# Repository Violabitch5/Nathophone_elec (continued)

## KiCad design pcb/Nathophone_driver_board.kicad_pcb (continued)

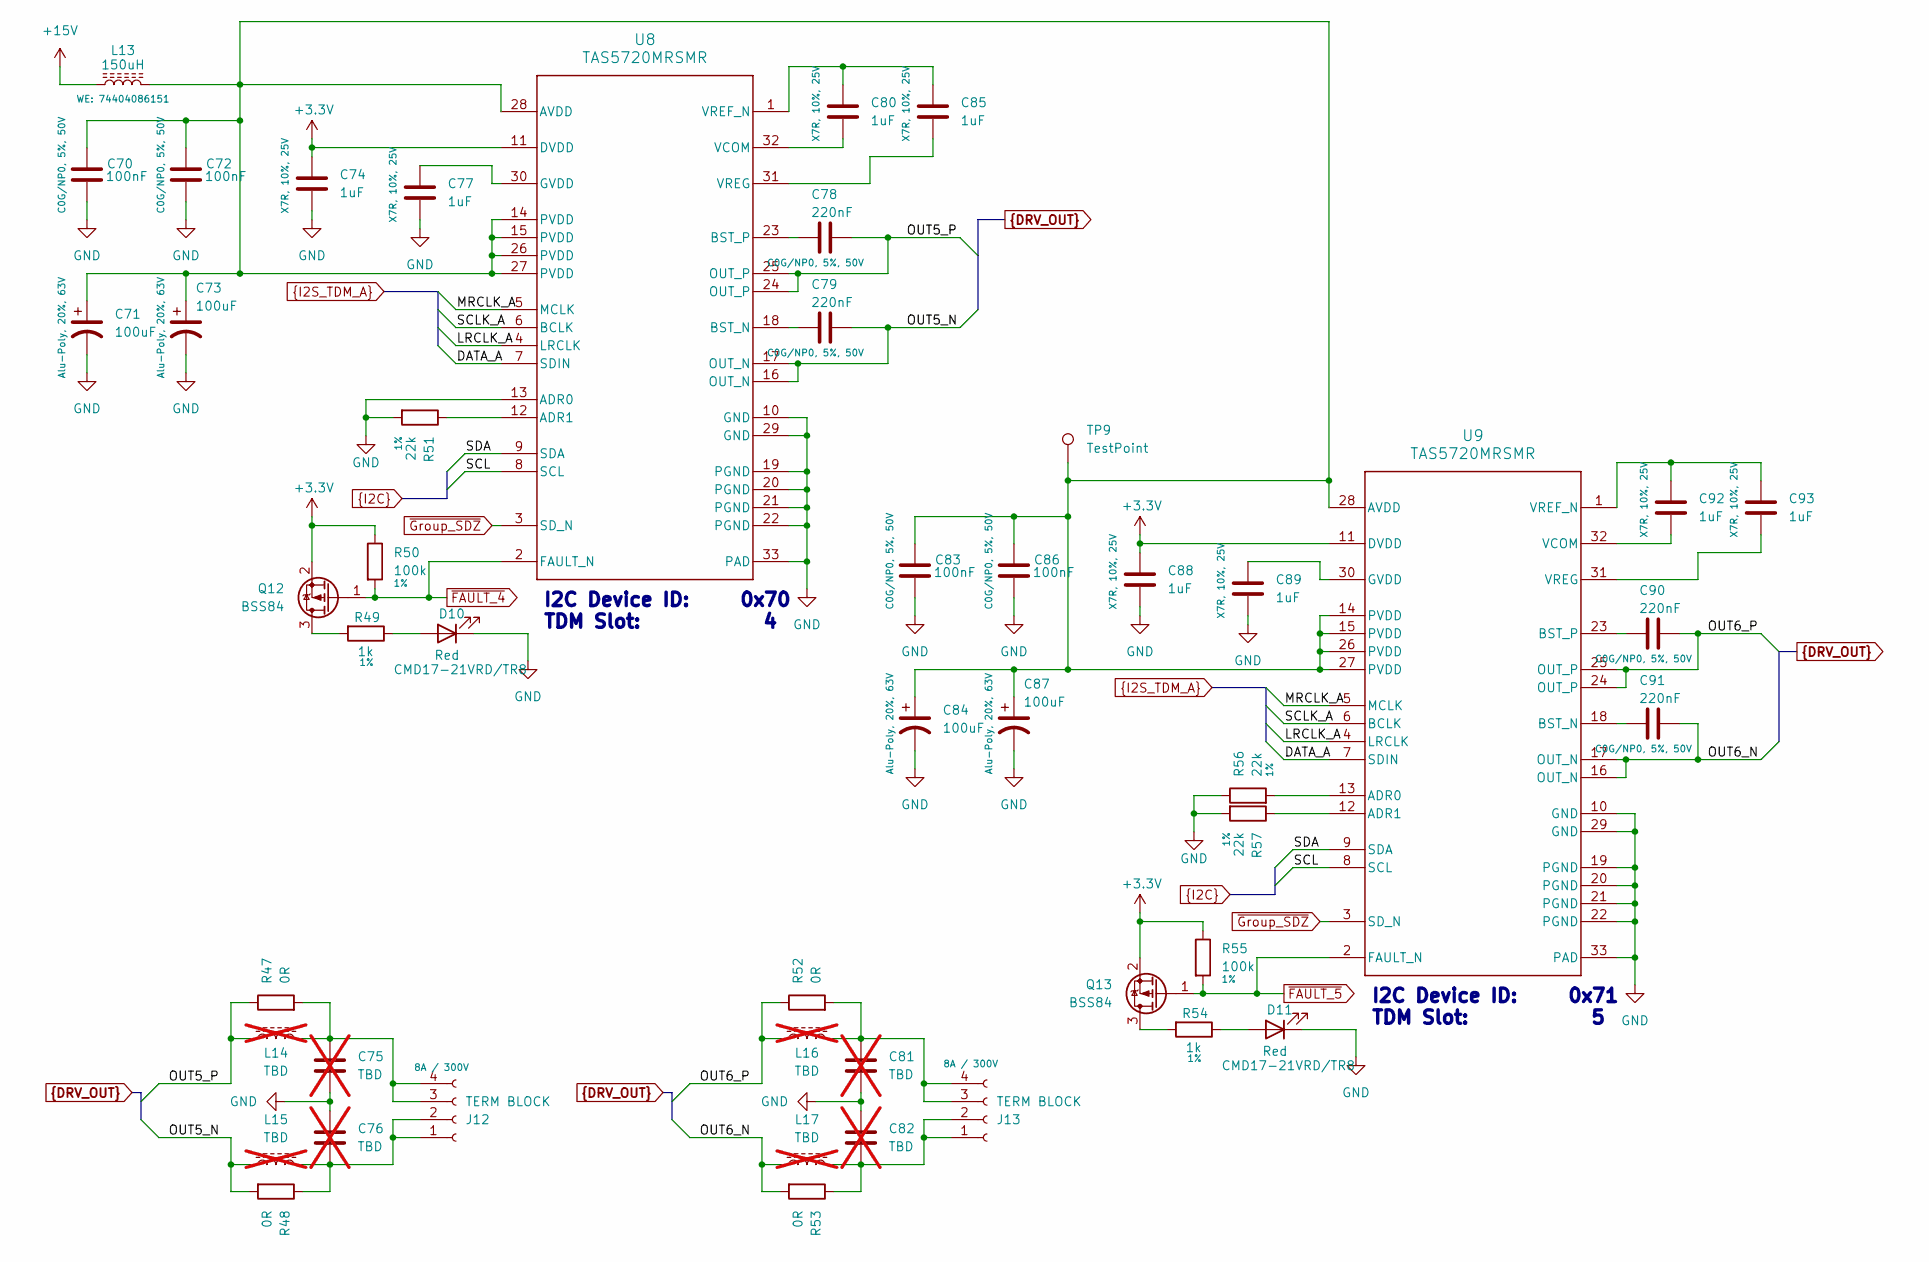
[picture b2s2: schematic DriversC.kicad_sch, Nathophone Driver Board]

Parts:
C70, C72, C83, C86: 100nF; C_1206_3216Metric; MPN GRM3195C1H104JA05D; DigiKey_PartNo 490-GRM3195C1H104JA05DTR-ND
C71, C73, C84, C87: 100uF; C_Elec_10x10.2; MPN A782MS107M1JLAS030; DigiKey_PartNo 399-A782MS107M1JLAS030TR-ND
C74, C77, C80, C85, C88, C89, C92, C93: 1uF; C_0805_2012Metric; MPN CL21B105KAFNNNE; DigiKey_PartNo 1276-1066-2-ND
C75, C76, C81, C82: TBD; C_2220_5750Metric; MPN SMDTC03680QB00MP00; DigiKey_PartNo 1928-1932-2-ND; not fitted
C78, C79, C90, C91: 220nF; C_1206_3216Metric; MPN GRM31C5C1H224JE02L; DigiKey_PartNo 490-GRM31C5C1H224JE02LTR-ND
D10, D11: CMD17-21VRD/TR8; LED_0805_2012Metric; MPN CMD17-21VRD/TR8; DigiKey_PartNo L62501TR-ND
J12, J13: TERM BLOCK; CONN_1862042; MPN 1862042; DigiKey_PartNo 277-12154-ND
L13: 150uH; WE-LQS_8065; MPN 74404086151; DigiKey_PartNo 732-11733-2-ND
L14, L15, L16, L17: TBD; IND_SRU1048-150Y; MPN SRU1048-150Y; DigiKey_PartNo SRU1048-150YTR-ND; not fitted
Q12, Q13: BSS84; SOT-23; MPN BSS84; DigiKey_PartNo 5399-BSS84TR-ND
R47, R48, R52, R53: 0R; R_2010_5025Metric; MPN CRCW20100000Z0EF; DigiKey_PartNo 541-0.0WTR-ND
R49, R54: 1k; R_0805_2012Metric; MPN CRCW08051K00FKEA; DigiKey_PartNo 541-1.00KCTR-ND
R50, R55: 100k; R_0805_2012Metric; MPN CRCW0805100KFKEA; DigiKey_PartNo 541-100KCTR-ND
R51, R56, R57: 22k; R_0805_2012Metric; MPN CRCW080522K0FKEB; DigiKey_PartNo 541-CRCW080522K0FKEBTR-ND
TP9: TestPoint; TestPoint_Pad_D2.0mm
U8, U9: TAS5720MRSMR; VQFN32_RSM0032B_NV; MPN TAS5720MRSMR; DigiKey_PartNo 296-TAS5720MRSMRTR-ND

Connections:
+3.3V: C74.1, C88.1, Q12.2 (S), Q13.2 (S), R50.1, R55.1, U8.11 (DVDD), U9.11 (DVDD); also elsewhere on the board
+15V: L13.1; also elsewhere on the board
DATA_A: U8.7 (SDIN), U9.7 (SDIN); also elsewhere on the board
GND: C70.2, C71.2, C72.2, C73.2, C74.2, C75.2, C76.1, C77.2, C81.2, C82.1, C83.2, C84.2, C86.2, C87.2, C88.2, C89.2, D10.1 (K), D11.1 (K), R51.2, R56.1, R57.2, U8.10 (GND), U8.13 (ADR0), U8.19 (PGND), U8.20 (PGND), U8.21 (PGND), U8.22 (PGND), U8.29 (GND), U8.33 (PAD), U9.10 (GND), U9.19 (PGND), U9.20 (PGND), U9.21 (PGND), U9.22 (PGND), U9.29 (GND), U9.33 (PAD); also elsewhere on the board
LRCLK_A: U8.4 (LRCLK), U9.4 (LRCLK); also elsewhere on the board
MRCLK_A: U8.5 (MCLK), U9.5 (MCLK); also elsewhere on the board
unnamed: D10.2 (A), R49.1
unnamed: D11.2 (A), R54.1
unnamed: C76.2, J12.1, J12.2, L15.2, R48.1
unnamed: C75.1, J12.3, J12.4, L14.2, R47.2
unnamed: C82.2, J13.1, J13.2, L17.2, R53.1
unnamed: C81.1, J13.3, J13.4, L16.2, R52.2
unnamed: Q12.3 (D), R49.2
unnamed: Q13.3 (D), R54.2
unnamed: R51.1, U8.12 (ADR1)
unnamed: C70.1, C71.1, C72.1, C73.1, C83.1, C84.1, C86.1, C87.1, L13.2, TP9.1, U8.14 (PVDD), U8.15 (PVDD), U8.26 (PVDD), U8.27 (PVDD), U8.28 (AVDD), U9.14 (PVDD), U9.15 (PVDD), U9.26 (PVDD), U9.27 (PVDD), U9.28 (AVDD)
unnamed: C79.1, U8.18 (BST_N)
unnamed: C78.1, U8.23 (BST_P)
unnamed: C77.1, U8.30 (GVDD)
unnamed: C80.2, U8.32 (VCOM)
unnamed: C80.1, C85.1, U8.1 (VREF_N)
unnamed: C85.2, U8.31 (VREG)
unnamed: R56.2, U9.13 (ADR0)
unnamed: R57.1, U9.12 (ADR1)
unnamed: C91.1, U9.18 (BST_N)
unnamed: C90.1, U9.23 (BST_P)
unnamed: C89.1, U9.30 (GVDD)
unnamed: C92.2, U9.32 (VCOM)
unnamed: C92.1, C93.1, U9.1 (VREF_N)
unnamed: C93.2, U9.31 (VREG)
OUT5_N: C79.2, L15.1, R48.2, U8.16 (OUT_N), U8.17 (OUT_N); also elsewhere on the board
OUT5_P: C78.2, L14.1, R47.1, U8.24 (OUT_P), U8.25 (OUT_P); also elsewhere on the board
OUT6_N: C91.2, L17.1, R53.2, U9.16 (OUT_N), U9.17 (OUT_N); also elsewhere on the board
OUT6_P: C90.2, L16.1, R52.1, U9.24 (OUT_P), U9.25 (OUT_P); also elsewhere on the board
SCL: U8.8 (SCL), U9.8 (SCL); also elsewhere on the board
SCLK_A: U8.6 (BCLK), U9.6 (BCLK); also elsewhere on the board
SDA: U8.9 (SDA), U9.9 (SDA); also elsewhere on the board
~FAULT_4: Q12.1 (G), R50.2, U8.2 (FAULT_N); also elsewhere on the board
~FAULT_5: Q13.1 (G), R55.2, U9.2 (FAULT_N); also elsewhere on the board
~Group_SDZ: U8.3 (SD_N), U9.3 (SD_N); also elsewhere on the board

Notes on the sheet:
I2C Device ID: 0x70 TDM Slot: 4
I2C Device ID: 0x71 TDM Slot: 5

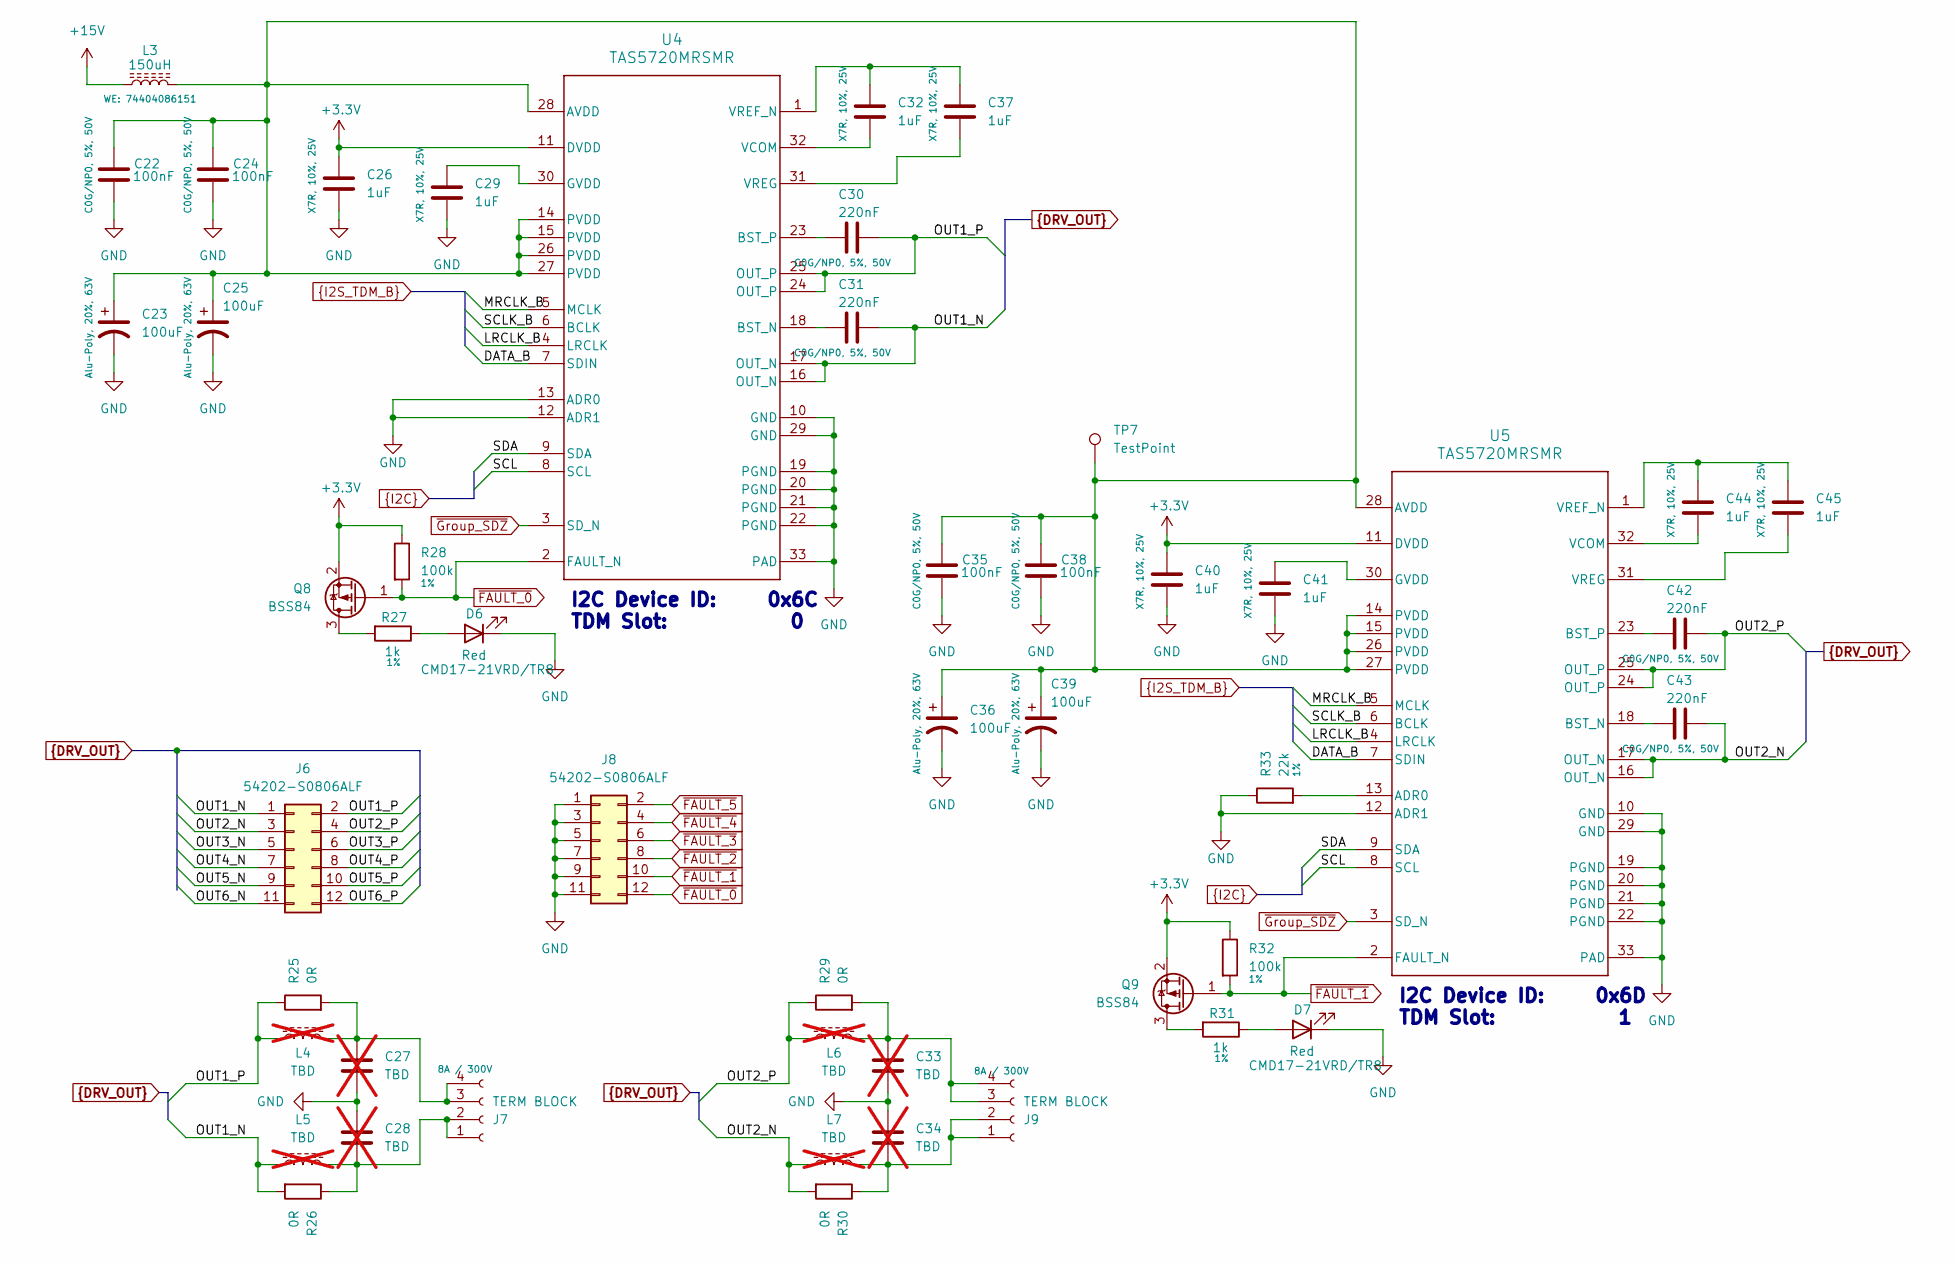
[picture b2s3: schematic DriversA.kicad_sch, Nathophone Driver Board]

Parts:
C22, C24, C35, C38: 100nF; C_1206_3216Metric; MPN GRM3195C1H104JA05D; DigiKey_PartNo 490-GRM3195C1H104JA05DTR-ND
C23, C25, C36, C39: 100uF; C_Elec_10x10.2; MPN A782MS107M1JLAS030; DigiKey_PartNo 399-A782MS107M1JLAS030TR-ND
C26, C29, C32, C37, C40, C41, C44, C45: 1uF; C_0805_2012Metric; MPN CL21B105KAFNNNE; DigiKey_PartNo 1276-1066-2-ND
C27, C28, C33, C34: TBD; C_2220_5750Metric; MPN SMDTC03680QB00MP00; DigiKey_PartNo 1928-1932-2-ND; not fitted
C30, C31, C42, C43: 220nF; C_1206_3216Metric; MPN GRM31C5C1H224JE02L; DigiKey_PartNo 490-GRM31C5C1H224JE02LTR-ND
D6, D7: CMD17-21VRD/TR8; LED_0805_2012Metric; MPN CMD17-21VRD/TR8; DigiKey_PartNo L62501TR-ND
J6, J8: 54202-S0806ALF; PinHeader_2x06_P2.54mm_Vertical_SMD; MPN 54202-S0806ALF; DigiKey_PartNo 609-54202-S0806ALFTR-ND
J7, J9: TERM BLOCK; CONN_1862042; MPN 1862042; DigiKey_PartNo 277-12154-ND
L3: 150uH; WE-LQS_8065; MPN 74404086151; DigiKey_PartNo 732-11733-2-ND
L4, L5, L6, L7: TBD; IND_SRU1048-150Y; MPN SRU1048-150Y; DigiKey_PartNo SRU1048-150YTR-ND; not fitted
Q8, Q9: BSS84; SOT-23; MPN BSS84; DigiKey_PartNo 5399-BSS84TR-ND
R25, R26, R29, R30: 0R; R_2010_5025Metric; MPN CRCW20100000Z0EF; DigiKey_PartNo 541-0.0WTR-ND
R27, R31: 1k; R_0805_2012Metric; MPN CRCW08051K00FKEA; DigiKey_PartNo 541-1.00KCTR-ND
R28, R32: 100k; R_0805_2012Metric; MPN CRCW0805100KFKEA; DigiKey_PartNo 541-100KCTR-ND
R33: 22k; R_0805_2012Metric; MPN CRCW080522K0FKEB; DigiKey_PartNo 541-CRCW080522K0FKEBTR-ND
TP7: TestPoint; TestPoint_Pad_D2.0mm
U4, U5: TAS5720MRSMR; VQFN32_RSM0032B_NV; MPN TAS5720MRSMR; DigiKey_PartNo 296-TAS5720MRSMRTR-ND

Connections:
+3.3V: C26.1, C40.1, Q8.2 (S), Q9.2 (S), R28.1, R32.1, U4.11 (DVDD), U5.11 (DVDD); also elsewhere on the board
+15V: L3.1; also elsewhere on the board
DATA_B: U4.7 (SDIN), U5.7 (SDIN); also elsewhere on the board
GND: C22.2, C23.2, C24.2, C25.2, C26.2, C27.2, C28.1, C29.2, C33.2, C34.1, C35.2, C36.2, C38.2, C39.2, C40.2, C41.2, D6.1 (K), D7.1 (K), J8.1, J8.3, J8.5, J8.7, J8.9, J8.11, R33.1, U4.10 (GND), U4.12 (ADR1), U4.13 (ADR0), U4.19 (PGND), U4.20 (PGND), U4.21 (PGND), U4.22 (PGND), U4.29 (GND), U4.33 (PAD), U5.10 (GND), U5.12 (ADR1), U5.19 (PGND), U5.20 (PGND), U5.21 (PGND), U5.22 (PGND), U5.29 (GND), U5.33 (PAD); also elsewhere on the board
LRCLK_B: U4.4 (LRCLK), U5.4 (LRCLK); also elsewhere on the board
MRCLK_B: U4.5 (MCLK), U5.5 (MCLK); also elsewhere on the board
unnamed: D6.2 (A), R27.1
unnamed: D7.2 (A), R31.1
unnamed: C28.2, J7.1, J7.2, L5.2, R26.1
unnamed: C27.1, J7.3, J7.4, L4.2, R25.2
unnamed: C34.2, J9.1, J9.2, L7.2, R30.1
unnamed: C33.1, J9.3, J9.4, L6.2, R29.2
unnamed: Q8.3 (D), R27.2
unnamed: Q9.3 (D), R31.2
unnamed: C22.1, C23.1, C24.1, C25.1, C35.1, C36.1, C38.1, C39.1, L3.2, TP7.1, U4.14 (PVDD), U4.15 (PVDD), U4.26 (PVDD), U4.27 (PVDD), U4.28 (AVDD), U5.14 (PVDD), U5.15 (PVDD), U5.26 (PVDD), U5.27 (PVDD), U5.28 (AVDD)
unnamed: C31.1, U4.18 (BST_N)
unnamed: C30.1, U4.23 (BST_P)
unnamed: C29.1, U4.30 (GVDD)
unnamed: C32.2, U4.32 (VCOM)
unnamed: C32.1, C37.1, U4.1 (VREF_N)
unnamed: C37.2, U4.31 (VREG)
unnamed: R33.2, U5.13 (ADR0)
unnamed: C43.1, U5.18 (BST_N)
unnamed: C42.1, U5.23 (BST_P)
unnamed: C41.1, U5.30 (GVDD)
unnamed: C44.2, U5.32 (VCOM)
unnamed: C44.1, C45.1, U5.1 (VREF_N)
unnamed: C45.2, U5.31 (VREG)
OUT1_N: C31.2, J6.1, L5.1, R26.2, U4.16 (OUT_N), U4.17 (OUT_N)
OUT1_P: C30.2, J6.2, L4.1, R25.1, U4.24 (OUT_P), U4.25 (OUT_P)
OUT2_N: C43.2, J6.3, L7.1, R30.2, U5.16 (OUT_N), U5.17 (OUT_N)
OUT2_P: C42.2, J6.4, L6.1, R29.1, U5.24 (OUT_P), U5.25 (OUT_P)
OUT3_N: J6.5; also elsewhere on the board
OUT3_P: J6.6; also elsewhere on the board
OUT4_N: J6.7; also elsewhere on the board
OUT4_P: J6.8; also elsewhere on the board
OUT5_N: J6.9; also elsewhere on the board
OUT5_P: J6.10; also elsewhere on the board
OUT6_N: J6.11; also elsewhere on the board
OUT6_P: J6.12; also elsewhere on the board
SCL: U4.8 (SCL), U5.8 (SCL); also elsewhere on the board
SCLK_B: U4.6 (BCLK), U5.6 (BCLK); also elsewhere on the board
SDA: U4.9 (SDA), U5.9 (SDA); also elsewhere on the board
~FAULT_0: J8.12, Q8.1 (G), R28.2, U4.2 (FAULT_N)
~FAULT_1: J8.10, Q9.1 (G), R32.2, U5.2 (FAULT_N)
~FAULT_2: J8.8; also elsewhere on the board
~FAULT_3: J8.6; also elsewhere on the board
~FAULT_4: J8.4; also elsewhere on the board
~FAULT_5: J8.2; also elsewhere on the board
~Group_SDZ: U4.3 (SD_N), U5.3 (SD_N); also elsewhere on the board

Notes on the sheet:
I2C Device ID: 0x6C TDM Slot: 0
I2C Device ID: 0x6D TDM Slot: 1

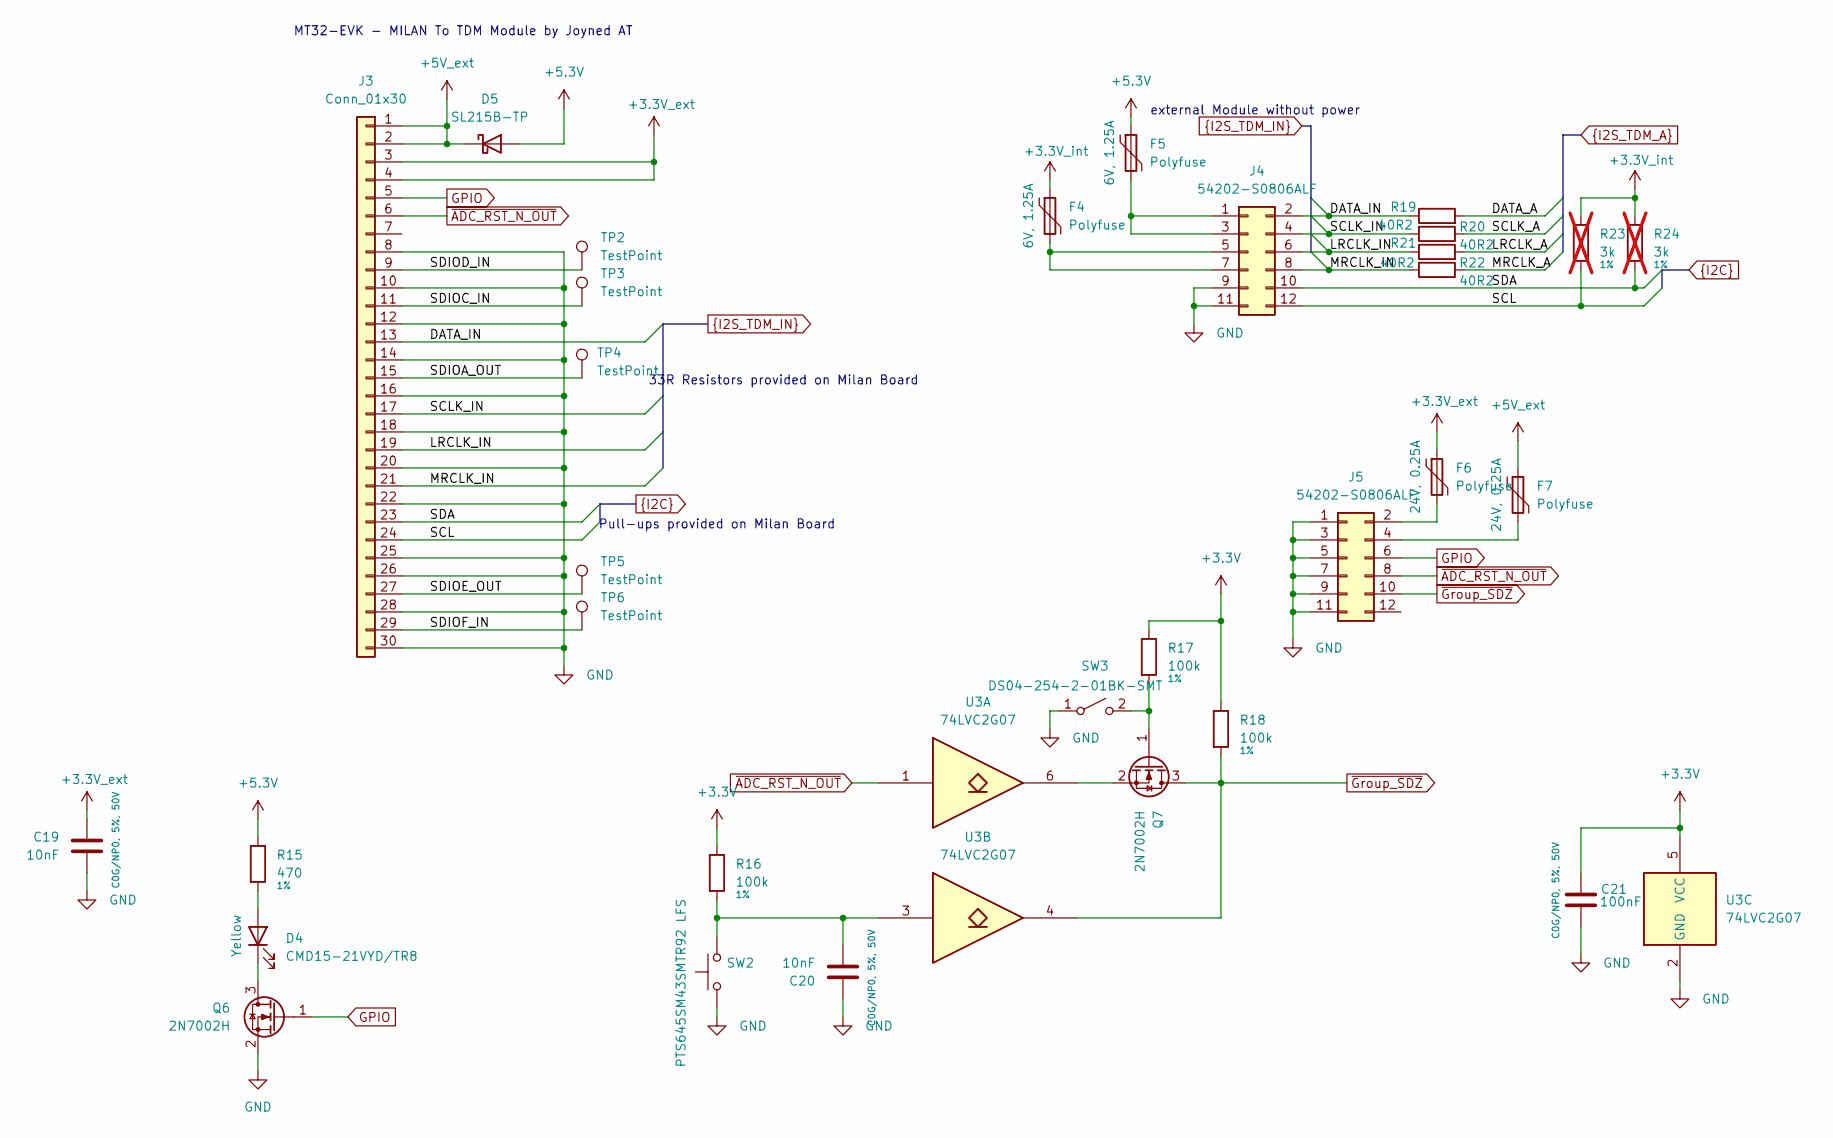
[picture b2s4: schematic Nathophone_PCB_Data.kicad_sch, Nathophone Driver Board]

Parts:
C19, C20: 10nF; C_0805_2012Metric; MPN CL21C103JBF1PNE; DigiKey_PartNo 1276-6790-2-ND
C21: 100nF; C_1206_3216Metric; MPN GRM3195C1H104JA05D; DigiKey_PartNo 490-GRM3195C1H104JA05DTR-ND
D4: CMD15-21VYD/TR8; LED_1206_3216Metric; MPN CMD15-21VYD/TR8; DigiKey_PartNo L62307TR-ND
D5: SL215B-TP; D_SMB; MPN SL215B-TP; DigiKey_PartNo 353-SL215B-TPTR-ND
F4, F5: Polyfuse; Fuse_1812_4532Metric; MPN MINISMDC125F-2; DigiKey_PartNo MINISMDC125F-2TR-ND
F6, F7: Polyfuse; Fuse_1206_3216Metric; MPN 0ZCJ0025AF2E; DigiKey_PartNo 5923-0ZCJ0025AF2ETR-ND
J3: Conn_01x30; CON_525593072_MOL; MPN 0525593072; DigiKey_PartNo 900-0525593072TR-ND
J4, J5: 54202-S0806ALF; PinHeader_2x06_P2.54mm_Vertical_SMD; MPN 54202-S0806ALF; DigiKey_PartNo 609-54202-S0806ALFTR-ND
Q6, Q7: 2N7002H; SOT-23; MPN 2N7002H-7; DigiKey_PartNo 2N7002H-7DITR-ND
R15: 470; R_0805_2012Metric; MPN CRCW0805470RJNEA; DigiKey_PartNo 541-470ATR-ND
R16, R17, R18: 100k; R_0805_2012Metric; MPN CRCW0805100KFKEA; DigiKey_PartNo 541-100KCTR-ND
R19, R20, R21, R22: 40R2; R_0805_2012Metric; MPN CRCW080540R2FKEA; DigiKey_PartNo 541-40.2CTR-ND
R23, R24: 3k; R_0805_2012Metric; MPN CRCW08053K00FKEA; DigiKey_PartNo 541-3.00KCTR-ND; not fitted
SW2: PTS645SM43SMTR92 LFS; SW_SPST_PTS645Sx43SMTR92; MPN PTS645SM43SMTR92 LFS; DigiKey_PartNo CKN9112TR-ND
SW3: DS04-254-2-01BK-SMT; SW_DS04-254-2-01BK-SMT; MPN DS04-254-2-01BK-SMT; DigiKey_PartNo 2223-DS04-254-2-01BK-SMT-ND
TP2, TP3, TP4, TP5, TP6: TestPoint; TestPoint_Pad_D2.0mm
U3: 74LVC2G07; SOT65P210X110-6N; MPN SN74LVC2G07DCKR; DigiKey_PartNo 296-13495-2-ND

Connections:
+3.3V: C21.1, R16.1, R17.1, R18.1, U3.5 (VCC); also elsewhere on the board
+3.3V_ext: C19.1, F6.1, J3.3, J3.4; also elsewhere on the board
+3.3V_int: F4.1, R23.1, R24.1; also elsewhere on the board
+5.3V: D5.2 (A), F5.1, R15.1; also elsewhere on the board
+5V_ext: D5.1 (K), F7.1, J3.1, J3.2
/Data+Power Connections/SDIOA_OUT: J3.15, TP4.1
/Data+Power Connections/SDIOC_IN: J3.11, TP3.1
/Data+Power Connections/SDIOD_IN: J3.9, TP2.1
/Data+Power Connections/SDIOE_OUT: J3.27, TP5.1
/Data+Power Connections/SDIOF_IN: J3.29, TP6.1
DATA_A: R19.2; also elsewhere on the board
DATA_IN: J3.13, J4.2, R19.1
GND: C19.2, C20.1, C21.2, J3.8, J3.10, J3.12, J3.14, J3.16, J3.18, J3.20, J3.22, J3.25, J3.26, J3.28, J3.30, J4.9, J4.11, J5.1, J5.3, J5.5, J5.7, J5.9, J5.11, Q6.2 (S), SW2.1, SW3.1 (A), U3.2 (GND); also elsewhere on the board
GPIO: J3.5, J5.6, Q6.1 (G)
LRCLK_A: R21.2; also elsewhere on the board
LRCLK_IN: J3.19, J4.6, R21.1
MRCLK_A: R22.1; also elsewhere on the board
MRCLK_IN: J3.21, J4.8, R22.2
unnamed: C20.2, R16.2, SW2.2, U3.3
unnamed: D4.2 (A), R15.2
unnamed: D4.1 (K), Q6.3 (D)
unnamed: F5.2, J4.1, J4.3
unnamed: F4.2, J4.5, J4.7
unnamed: F6.2, J5.2
unnamed: F7.2, J5.4
unnamed: Q7.1 (G), R17.2, SW3.2 (B)
unnamed: Q7.2 (S), U3.6
SCL: J3.24, J4.12, R23.2; also elsewhere on the board
SCLK_A: R20.1; also elsewhere on the board
SCLK_IN: J3.17, J4.4, R20.2
SDA: J3.23, J4.10, R24.2; also elsewhere on the board
~ADC_RST_N_OUT: J3.6, J5.8, U3.1
~Group_SDZ: J5.10, Q7.3 (D), R18.2, U3.4; also elsewhere on the board

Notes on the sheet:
MT32-EVK - MILAN To TDM Module by Joyned AT
external Module without power
33R Resistors provided on Milan Board
Pull-ups provided on Milan Board

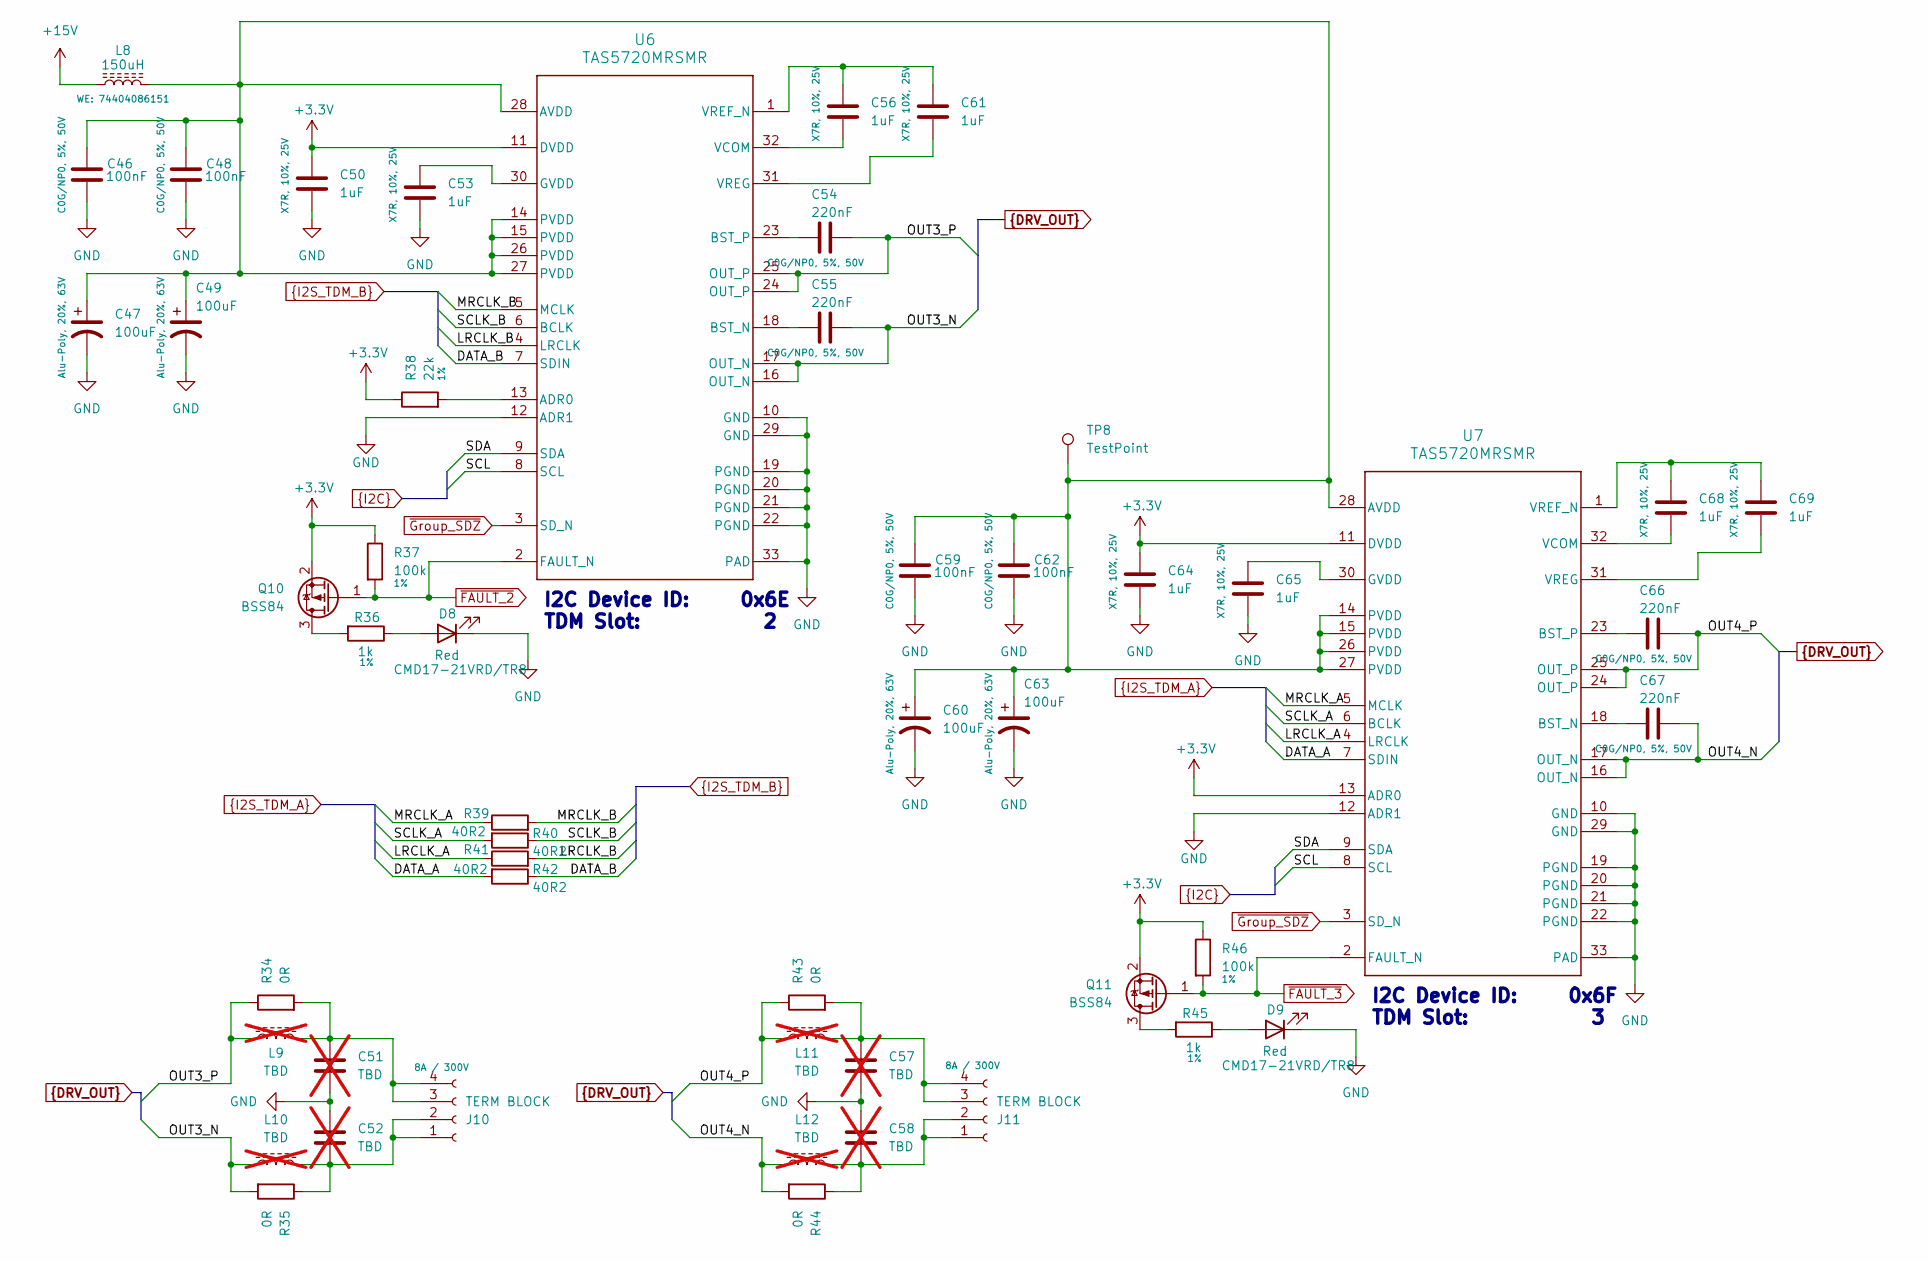
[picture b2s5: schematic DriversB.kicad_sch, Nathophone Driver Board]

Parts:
C46, C48, C59, C62: 100nF; C_1206_3216Metric; MPN GRM3195C1H104JA05D; DigiKey_PartNo 490-GRM3195C1H104JA05DTR-ND
C47, C49, C60, C63: 100uF; C_Elec_10x10.2; MPN A782MS107M1JLAS030; DigiKey_PartNo 399-A782MS107M1JLAS030TR-ND
C50, C53, C56, C61, C64, C65, C68, C69: 1uF; C_0805_2012Metric; MPN CL21B105KAFNNNE; DigiKey_PartNo 1276-1066-2-ND
C51, C52, C57, C58: TBD; C_2220_5750Metric; MPN SMDTC03680QB00MP00; DigiKey_PartNo 1928-1932-2-ND; not fitted
C54, C55, C66, C67: 220nF; C_1206_3216Metric; MPN GRM31C5C1H224JE02L; DigiKey_PartNo 490-GRM31C5C1H224JE02LTR-ND
D8, D9: CMD17-21VRD/TR8; LED_0805_2012Metric; MPN CMD17-21VRD/TR8; DigiKey_PartNo L62501TR-ND
J10, J11: TERM BLOCK; CONN_1862042; MPN 1862042; DigiKey_PartNo 277-12154-ND
L8: 150uH; WE-LQS_8065; MPN 74404086151; DigiKey_PartNo 732-11733-2-ND
L9, L10, L11, L12: TBD; IND_SRU1048-150Y; MPN SRU1048-150Y; DigiKey_PartNo SRU1048-150YTR-ND; not fitted
Q10, Q11: BSS84; SOT-23; MPN BSS84; DigiKey_PartNo 5399-BSS84TR-ND
R34, R35, R43, R44: 0R; R_2010_5025Metric; MPN CRCW20100000Z0EF; DigiKey_PartNo 541-0.0WTR-ND
R36, R45: 1k; R_0805_2012Metric; MPN CRCW08051K00FKEA; DigiKey_PartNo 541-1.00KCTR-ND
R37, R46: 100k; R_0805_2012Metric; MPN CRCW0805100KFKEA; DigiKey_PartNo 541-100KCTR-ND
R38: 22k; R_0805_2012Metric; MPN CRCW080522K0FKEB; DigiKey_PartNo 541-CRCW080522K0FKEBTR-ND
R39, R40, R41, R42: 40R2; R_0805_2012Metric; MPN CRCW080540R2FKEA; DigiKey_PartNo 541-40.2CTR-ND
TP8: TestPoint; TestPoint_Pad_D2.0mm
U6, U7: TAS5720MRSMR; VQFN32_RSM0032B_NV; MPN TAS5720MRSMR; DigiKey_PartNo 296-TAS5720MRSMRTR-ND

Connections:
+3.3V: C50.1, C64.1, Q10.2 (S), Q11.2 (S), R37.1, R38.1, R46.1, U6.11 (DVDD), U7.11 (DVDD), U7.13 (ADR0); also elsewhere on the board
+15V: L8.1; also elsewhere on the board
DATA_A: R42.2, U7.7 (SDIN); also elsewhere on the board
DATA_B: R42.1, U6.7 (SDIN); also elsewhere on the board
GND: C46.2, C47.2, C48.2, C49.2, C50.2, C51.2, C52.1, C53.2, C57.2, C58.1, C59.2, C60.2, C62.2, C63.2, C64.2, C65.2, D8.1 (K), D9.1 (K), U6.10 (GND), U6.12 (ADR1), U6.19 (PGND), U6.20 (PGND), U6.21 (PGND), U6.22 (PGND), U6.29 (GND), U6.33 (PAD), U7.10 (GND), U7.12 (ADR1), U7.19 (PGND), U7.20 (PGND), U7.21 (PGND), U7.22 (PGND), U7.29 (GND), U7.33 (PAD); also elsewhere on the board
LRCLK_A: R41.1, U7.4 (LRCLK); also elsewhere on the board
LRCLK_B: R41.2, U6.4 (LRCLK); also elsewhere on the board
MRCLK_A: R39.1, U7.5 (MCLK); also elsewhere on the board
MRCLK_B: R39.2, U6.5 (MCLK); also elsewhere on the board
unnamed: D8.2 (A), R36.1
unnamed: D9.2 (A), R45.1
unnamed: C52.2, J10.1, J10.2, L10.2, R35.1
unnamed: C51.1, J10.3, J10.4, L9.2, R34.2
unnamed: C58.2, J11.1, J11.2, L12.2, R44.1
unnamed: C57.1, J11.3, J11.4, L11.2, R43.2
unnamed: Q10.3 (D), R36.2
unnamed: Q11.3 (D), R45.2
unnamed: R38.2, U6.13 (ADR0)
unnamed: C46.1, C47.1, C48.1, C49.1, C59.1, C60.1, C62.1, C63.1, L8.2, TP8.1, U6.14 (PVDD), U6.15 (PVDD), U6.26 (PVDD), U6.27 (PVDD), U6.28 (AVDD), U7.14 (PVDD), U7.15 (PVDD), U7.26 (PVDD), U7.27 (PVDD), U7.28 (AVDD)
unnamed: C55.1, U6.18 (BST_N)
unnamed: C54.1, U6.23 (BST_P)
unnamed: C53.1, U6.30 (GVDD)
unnamed: C56.2, U6.32 (VCOM)
unnamed: C56.1, C61.1, U6.1 (VREF_N)
unnamed: C61.2, U6.31 (VREG)
unnamed: C67.1, U7.18 (BST_N)
unnamed: C66.1, U7.23 (BST_P)
unnamed: C65.1, U7.30 (GVDD)
unnamed: C68.2, U7.32 (VCOM)
unnamed: C68.1, C69.1, U7.1 (VREF_N)
unnamed: C69.2, U7.31 (VREG)
OUT3_N: C55.2, L10.1, R35.2, U6.16 (OUT_N), U6.17 (OUT_N); also elsewhere on the board
OUT3_P: C54.2, L9.1, R34.1, U6.24 (OUT_P), U6.25 (OUT_P); also elsewhere on the board
OUT4_N: C67.2, L12.1, R44.2, U7.16 (OUT_N), U7.17 (OUT_N); also elsewhere on the board
OUT4_P: C66.2, L11.1, R43.1, U7.24 (OUT_P), U7.25 (OUT_P); also elsewhere on the board
SCL: U6.8 (SCL), U7.8 (SCL); also elsewhere on the board
SCLK_A: R40.2, U7.6 (BCLK); also elsewhere on the board
SCLK_B: R40.1, U6.6 (BCLK); also elsewhere on the board
SDA: U6.9 (SDA), U7.9 (SDA); also elsewhere on the board
~FAULT_2: Q10.1 (G), R37.2, U6.2 (FAULT_N); also elsewhere on the board
~FAULT_3: Q11.1 (G), R46.2, U7.2 (FAULT_N); also elsewhere on the board
~Group_SDZ: U6.3 (SD_N), U7.3 (SD_N); also elsewhere on the board

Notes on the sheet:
I2C Device ID: 0x6F TDM Slot: 3
I2C Device ID: 0x6E TDM Slot: 2

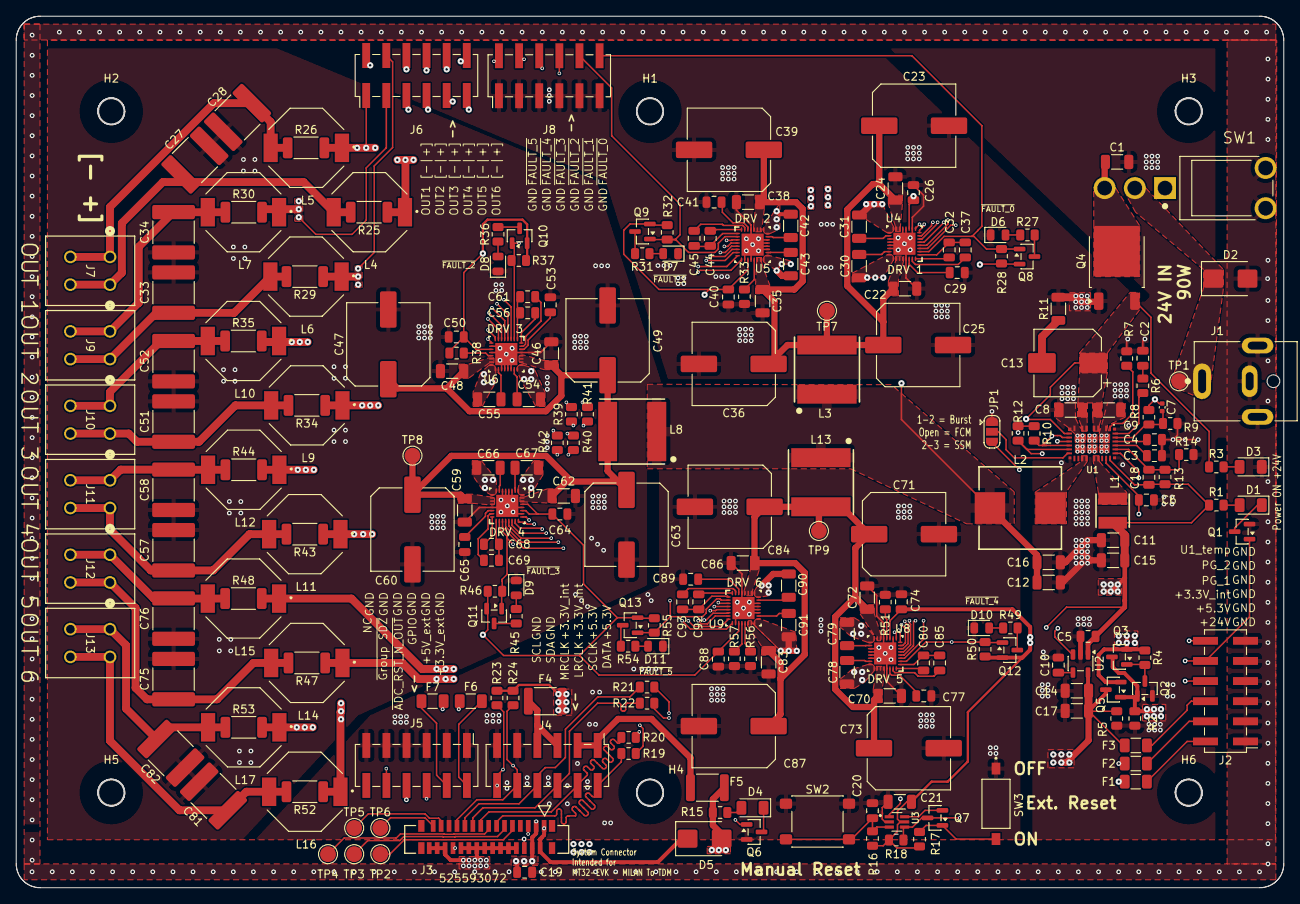
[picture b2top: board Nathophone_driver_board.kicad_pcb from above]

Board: 4 copper layers, 160.0 x 110.0 mm, 239 parts (0 on the bottom side), 150 nets.

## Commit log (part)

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2025-07-29 Initial Commit, First part evaluations added
2025-10-12 ADDED Symbols,footprints, simulations ,datasheet, sample schematic
2025-10-16 BEGUN Layout
2025-10-17 ADDED Grounding Structure
2025-10-17 DONE Routing first two drivers
2025-10-17 DONE Digital Routing
2025-10-17 COMPLETED Routing, DRC checked
2025-10-18 CHANGED Output and Power Track widths to 1mm
2025-10-18 FINISHED Version 1, Checked heights
2025-10-18 CHANGED small things, removed tiny 0201 cap
2025-10-19 CHANGED little tweaks in the Ground path, removed unnecessary Diode
2025-10-24 SIMULATED Transmission line, LAST checks, ORDERED pcb
2025-11-09 ADDED Efficiency Report
2025-12-14 CORRECTED TVS Diode polarisation
2025-12-18 ADDED Supply Startup Measurements
2026-05-07 ADDED JOYNED Design files, BEGUN USBtoI2S Design
2026-05-14 ADDED XMOS eval board design files, BEGUN layout of usbtoi2s board
2026-05-14 PLACED all footprints and GND zone
2026-05-19 CONTINUED LAYOUT, MAIN Connections
2026-05-20 CONTINUED main layout
2026-05-21 COMPLETED first version of Layout
